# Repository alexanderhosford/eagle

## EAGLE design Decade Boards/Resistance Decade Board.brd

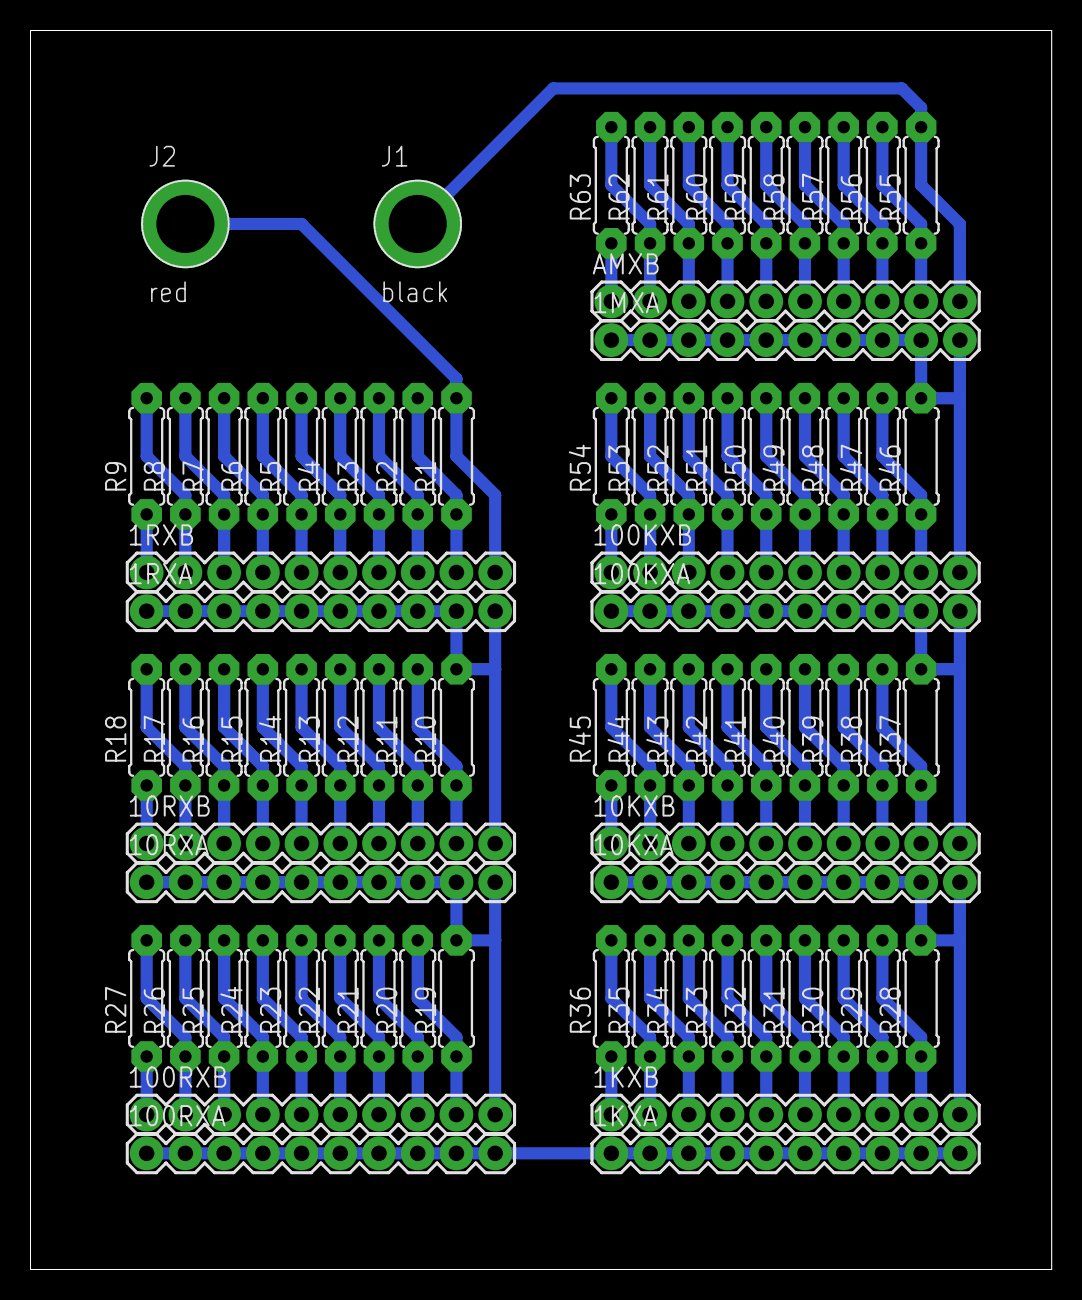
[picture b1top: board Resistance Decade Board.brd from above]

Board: 2 copper layers, 67.0 x 81.3 mm, 79 parts (0 on the bottom side), 71 nets.

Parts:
1KXA, 1KXB, 1MXA, 1RXA, 1RXB, 10KXA, 10KXB, 10RXA, 10RXB, 100KXA, 100KXB, 100RXA, 100RXB: M10"; 1X10
AMXB: M10"; 1X10
J1: black; BANANA_CONN
J2: red; BANANA_CONN
R1, R2, R3, R4, R5, R6, R7, R8, R9: 1R; 0207/7
R10, R11, R12, R13, R14, R15, R16, R17, R18: 10R; 0207/7
R19, R20, R21, R22, R23, R24, R25, R26, R27: 100R; 0207/7
R28, R29, R30, R31, R32, R33, R34, R35, R36: 1k; 0207/7
R37, R38, R39, R40, R41, R42, R43, R44, R45: 10k; 0207/7
R46, R47, R48, R49, R50, R51, R52, R53, R54: 100k; 0207/7
R55, R56, R57, R58, R59, R60, R61, R62, R63: 1M; 0207/7

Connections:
100KX: 100KXB.8, R47.1, R48.2
unnamed: 1RXB.2, R8.1, R9.2
unnamed: 1RXB.3, R7.1, R8.2
unnamed: 1RXB.4, R6.1, R7.2
unnamed: 1RXB.5, R5.1, R6.2
unnamed: 1RXB.6, R4.1, R5.2
unnamed: 1RXB.7, R3.1, R4.2
unnamed: 1RXB.8, R2.1, R3.2
unnamed: 1RXB.9, R1.1, R2.2
unnamed: 1RXB.10, J2.P$1, R1.2
unnamed: 1RXA.1, 1RXA.2, 1RXA.3, 1RXA.4, 1RXA.5, 1RXA.6, 1RXA.7, 1RXA.8, 1RXA.9, 1RXA.10, 10RXB.10, R10.2
unnamed: 10RXA.1, 10RXA.2, 10RXA.3, 10RXA.4, 10RXA.5, 10RXA.6, 10RXA.7, 10RXA.8, 10RXA.9, 10RXA.10, 100RXB.10, R19.2
unnamed: 1KXB.10, 10KXA.1, 10KXA.2, 10KXA.3, 10KXA.4, 10KXA.5, 10KXA.6, 10KXA.7, 10KXA.8, 10KXA.9, 10KXA.10, R28.2
unnamed: 10KXB.10, 100KXA.1, 100KXA.2, 100KXA.3, 100KXA.4, 100KXA.5, 100KXA.6, 100KXA.7, 100KXA.8, 100KXA.9, 100KXA.10, R37.2
unnamed: AMXB.10, J1.P$1, R55.2
unnamed: 1RXB.1, R9.1
unnamed: 10RXB.2, R17.1, R18.2
unnamed: 10RXB.3, R16.1, R17.2
unnamed: 10RXB.4, R15.1, R16.2
unnamed: 10RXB.5, R14.1, R15.2
unnamed: 10RXB.6, R13.1, R14.2
unnamed: 10RXB.7, R12.1, R13.2
unnamed: 10RXB.8, R11.1, R12.2
unnamed: 10RXB.9, R10.1, R11.2
unnamed: 10RXB.1, R18.1
unnamed: 100RXB.2, R26.1, R27.2
unnamed: 100RXB.3, R25.1, R26.2
unnamed: 100RXB.4, R24.1, R25.2
unnamed: 100RXB.5, R23.1, R24.2
unnamed: 100RXB.6, R22.1, R23.2
unnamed: 100RXB.7, R21.1, R22.2
unnamed: 100RXB.8, R20.1, R21.2
unnamed: 100RXB.9, R19.1, R20.2
unnamed: 100RXB.1, R27.1
unnamed: 1KXB.2, R35.1, R36.2
unnamed: 1KXB.3, R34.1, R35.2
unnamed: 1KXB.4, R33.1, R34.2
unnamed: 1KXB.5, R32.1, R33.2
unnamed: 1KXB.6, R31.1, R32.2
unnamed: 1KXB.7, R30.1, R31.2
unnamed: 1KXB.8, R29.1, R30.2
unnamed: 1KXB.9, R28.1, R29.2
unnamed: 1KXB.1, R36.1
unnamed: 10KXB.2, R44.1, R45.2
unnamed: 10KXB.3, R43.1, R44.2
unnamed: 10KXB.4, R42.1, R43.2
unnamed: 10KXB.5, R41.1, R42.2
unnamed: 10KXB.6, R40.1, R41.2
unnamed: 10KXB.7, R39.1, R40.2
unnamed: 10KXB.8, R38.1, R39.2
unnamed: 10KXB.9, R37.1, R38.2
unnamed: 10KXB.1, R45.1
unnamed: 100KXB.2, R53.1, R54.2
unnamed: 100KXB.3, R52.1, R53.2
unnamed: 100KXB.4, R51.1, R52.2
unnamed: 100KXB.5, R50.1, R51.2
unnamed: 100KXB.6, R49.1, R50.2
unnamed: 100KXB.7, R48.1, R49.2
unnamed: 100KXB.9, R46.1, R47.2
unnamed: 100KXB.1, R54.1
unnamed: AMXB.2, R62.1, R63.2
unnamed: AMXB.3, R61.1, R62.2
unnamed: AMXB.4, R60.1, R61.2
unnamed: AMXB.5, R59.1, R60.2
unnamed: AMXB.6, R58.1, R59.2
unnamed: AMXB.7, R57.1, R58.2
unnamed: AMXB.8, R56.1, R57.2
unnamed: AMXB.9, R55.1, R56.2
unnamed: AMXB.1, R63.1
unnamed: 1MXA.1, 1MXA.2, 1MXA.3, 1MXA.4, 1MXA.5, 1MXA.6, 1MXA.7, 1MXA.8, 1MXA.9, 1MXA.10, 100KXB.10, R46.2
unnamed: 1KXA.1, 1KXA.2, 1KXA.3, 1KXA.4, 1KXA.5, 1KXA.6, 1KXA.7, 1KXA.8, 1KXA.9, 1KXA.10, 100RXA.1, 100RXA.2, 100RXA.3, 100RXA.4, 100RXA.5, 100RXA.6, 100RXA.7, 100RXA.8, 100RXA.9, 100RXA.10

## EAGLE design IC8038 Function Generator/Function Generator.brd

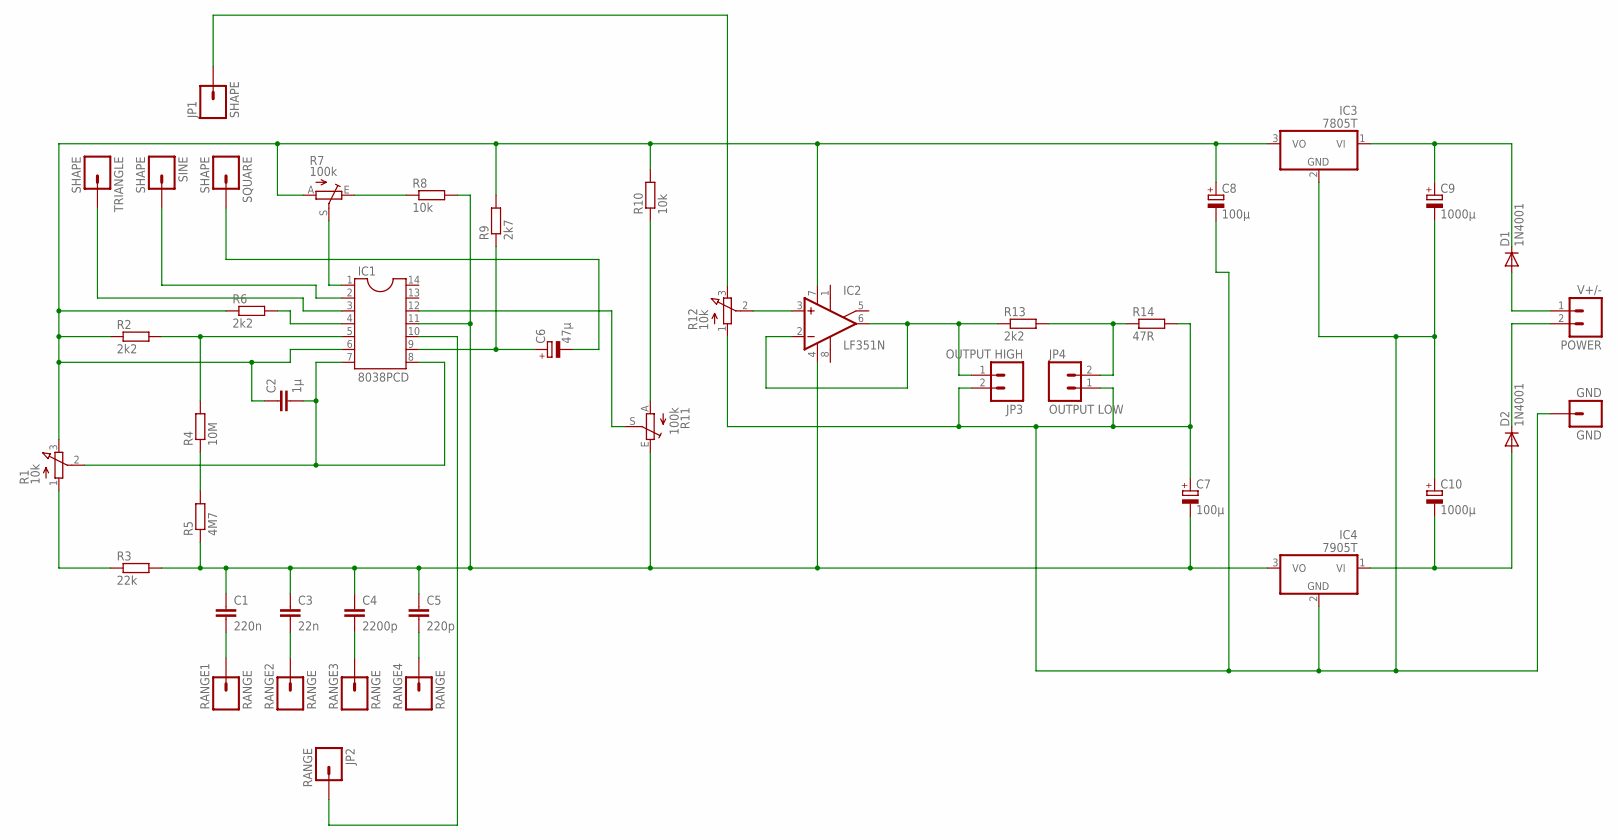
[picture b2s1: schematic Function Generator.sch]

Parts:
C1: 220n; C050-035X075
C2: 1µ; C050-035X075
C3: 22n; C050-035X075
C4: 2200p; C050-035X075
C5: 220p; C050-035X075
C6: 47µ; E5-10,5
C7, C8: 100µ; E3,5-8
C9, C10: 1000µ; E5-10,5
D1, D2: 1N4001; DO41-10
GND: GND; 1X01_LONGPAD
IC1: 8038PCD; DIL14
IC2: LF351N; DIL08
IC3: 7805T; TO220H
IC4: 7905T; TO220H
JP1: SHAPE; 1X01_LONGPAD
JP2: RANGE; 1X01_LONGPAD
JP3: OUTPUT HIGH; SCREWTERMINAL-3.5MM-2
JP4: OUTPUT LOW; SCREWTERMINAL-3.5MM-2
POWER: V+/-; SCREWTERMINAL-3.5MM-2
R1, R12: 10k; 3RP/1610N
R2, R6, R13: 2k2; 0207/10
R3: 22k; 0207/10
R4: 10M; 0207/10
R5: 4M7; 0207/10
R7, R11: 100k; S64Y
R8, R10: 10k; 0207/10
R9: 2k7; 0207/10
R14: 47R; 0207/10
RANGE1, RANGE2, RANGE3, RANGE4: RANGE; 1X01_LONGPAD
SINE: SHAPE; 1X01_LONGPAD
SQUARE: SHAPE; 1X01_LONGPAD
TRIANGLE: SHAPE; 1X01_LONGPAD

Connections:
GND: C7.+, C8.-, C9.-, C10.+, GND.1, IC3.2 (GND), IC4.2 (GND), JP3.2, JP4.1, R12.1 (A), R14.2
unnamed: IC1.4 (DUTYCYCLE), R6.2
unnamed: IC1.5 (FREQUENCYADJUST), R2.2, R4.2
unnamed: C2.1, C8.+, IC1.6 (V+), IC2.7 (V+), IC3.3 (VO), R1.3 (E), R2.1, R6.1, R7.A, R9.2, R10.2
unnamed: C2.2, IC1.7 (FMBIAS), IC1.8 (FMSWEEPINPUT), R1.2 (S)
unnamed: R4.1, R5.2
unnamed: C1.1, C3.1, C4.1, C5.1, C7.-, IC1.11 (V-ORGROUND), IC2.4 (V-), IC4.3 (VO), R3.2, R5.1, R8.2, R11.E
unnamed: R1.1 (A), R3.1
unnamed: C3.2, RANGE2.1
unnamed: C4.2, RANGE3.1
unnamed: C1.2, RANGE1.1
unnamed: C5.2, RANGE4.1
unnamed: IC1.10 (TIMINGCAPACITOR), JP2.1
unnamed: C6.+, IC1.9 (SQUAREWAVEOUT), R9.1
unnamed: R7.E, R8.1
unnamed: IC2.2 (-IN), IC2.6 (OUT), JP3.1, R13.1
unnamed: IC1.3 (TRIANGLEOUT), TRIANGLE.1
unnamed: IC1.2 (SINEWAVEOUT), SINE.1
unnamed: IC1.1 (SINEWAVEADJUST), R7.S
unnamed: C6.-, SQUARE.1
unnamed: R10.1, R11.A
unnamed: IC1.12 (SINEWAVEADJUST2), R11.S
unnamed: IC2.3 (+IN), R12.2 (S)
unnamed: JP1.1, R12.3 (E)
unnamed: JP4.2, R13.2, R14.1
unnamed: C10.-, D2.A, IC4.1 (VI)
unnamed: C9.+, D1.C, IC3.1 (VI)
unnamed: D1.A, POWER.1
unnamed: D2.C, POWER.2

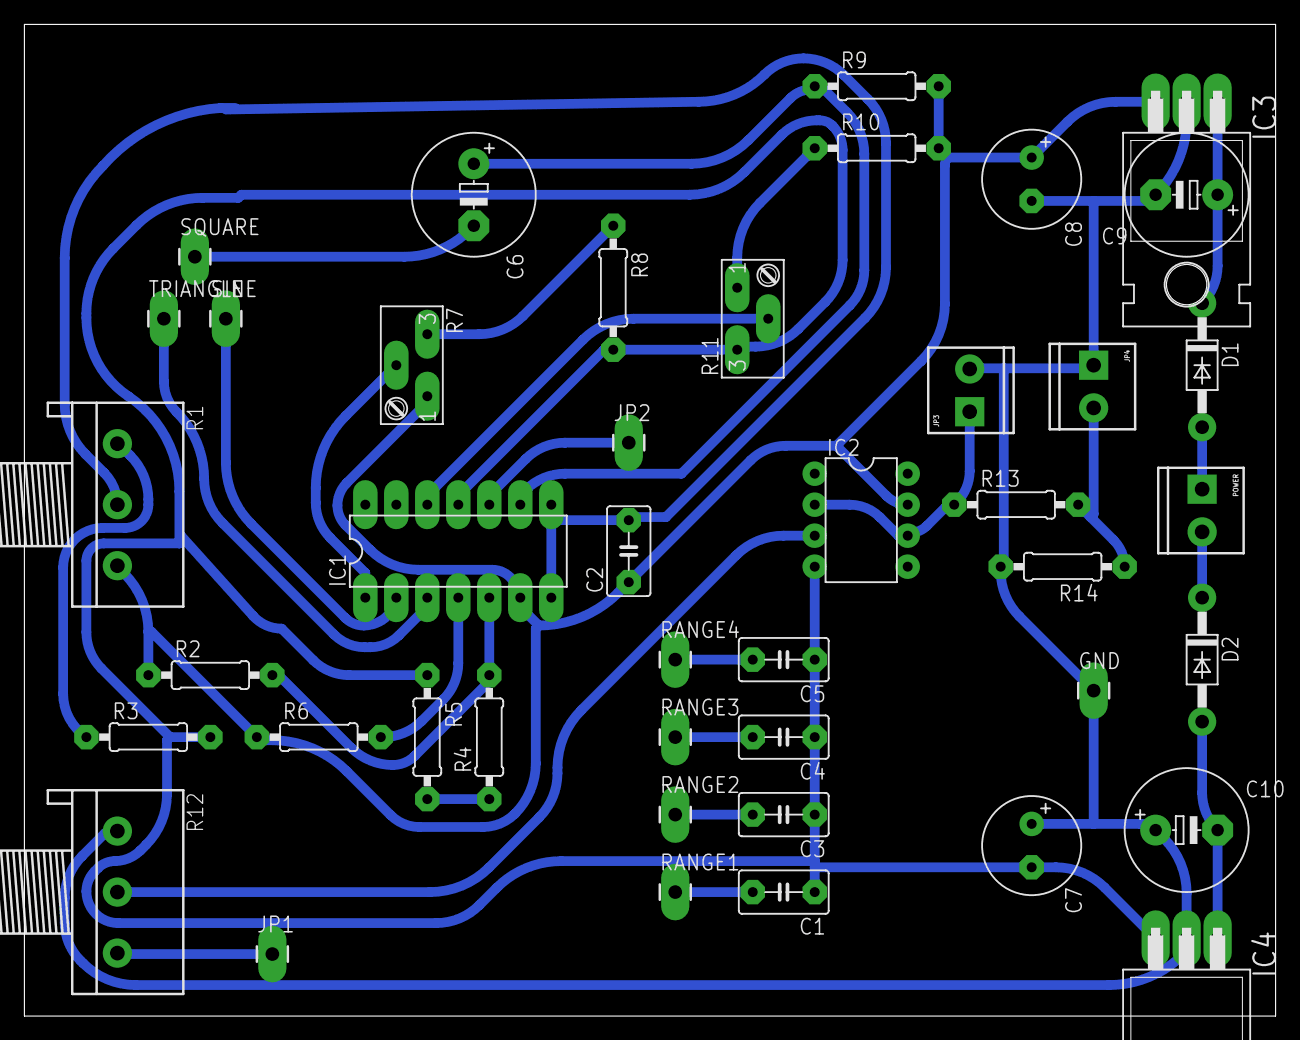
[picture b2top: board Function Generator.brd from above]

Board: 2 copper layers, 102.5 x 81.3 mm, 43 parts (0 on the bottom side), 29 nets.

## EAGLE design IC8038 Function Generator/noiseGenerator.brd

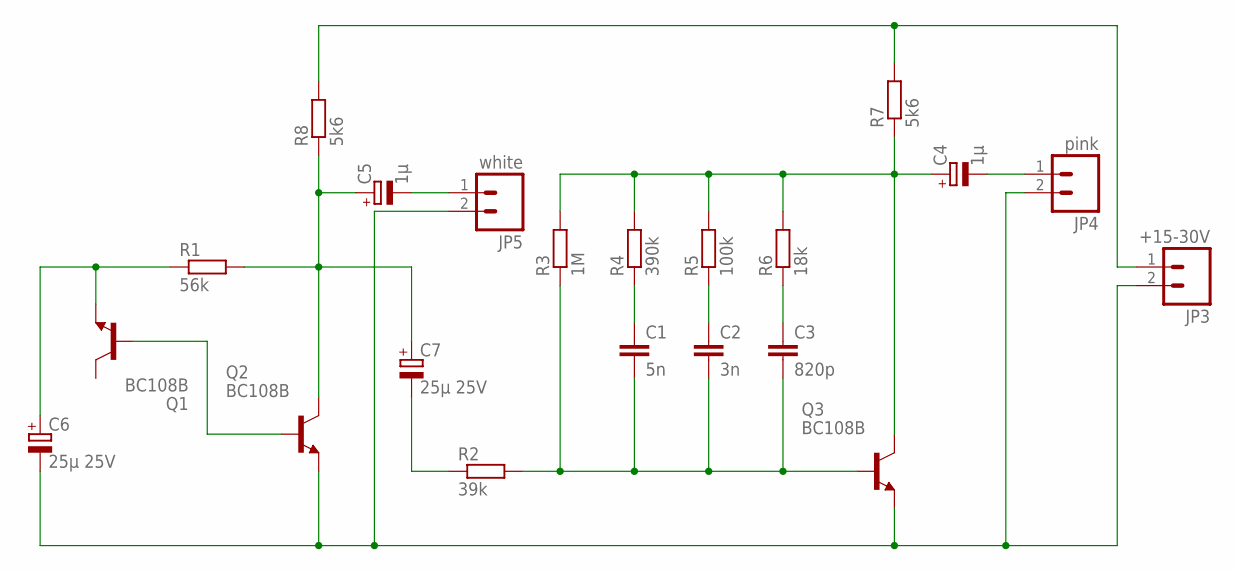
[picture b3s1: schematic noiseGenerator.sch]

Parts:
C1: 5n; C050-035X075
C2: 3n; C050-035X075
C3: 820p; C050-035X075
C4, C5: 1µ; E5-8,5
C6, C7: 25µ 25V; E5-8,5
JP3: +15-30V; SCREWTERMINAL-3.5MM-2
JP4: pink; SCREWTERMINAL-3.5MM-2
JP5: white; SCREWTERMINAL-3.5MM-2
Q1, Q2, Q3: BC108B; TO18
R1: 56k; 0207/10
R2: 39k; 0207/10
R3: 1M; 0207/10
R4: 390k; 0207/10
R5: 100k; 0207/10
R6: 18k; 0207/10
R7, R8: 5k6; 0207/10

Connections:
GND: C6.-, JP3.2, JP4.2, JP5.2, Q2.1 (E), Q3.1 (E)
unnamed: C4.-, JP4.1
unnamed: C4.+, Q3.3 (C), R3.2, R4.2, R5.2, R6.2, R7.1
unnamed: C1.1, R4.1
unnamed: C2.1, R5.1
unnamed: C3.1, R6.1
unnamed: C1.2, C2.2, C3.2, Q3.2 (B), R2.2, R3.1
unnamed: JP3.1, R7.2, R8.2
unnamed: C5.+, C7.+, Q2.3 (C), R1.2, R8.1
unnamed: C5.-, JP5.1
unnamed: C7.-, R2.1
unnamed: C6.+, Q1.1 (E), R1.1
unnamed: Q1.2 (B), Q2.2 (B)

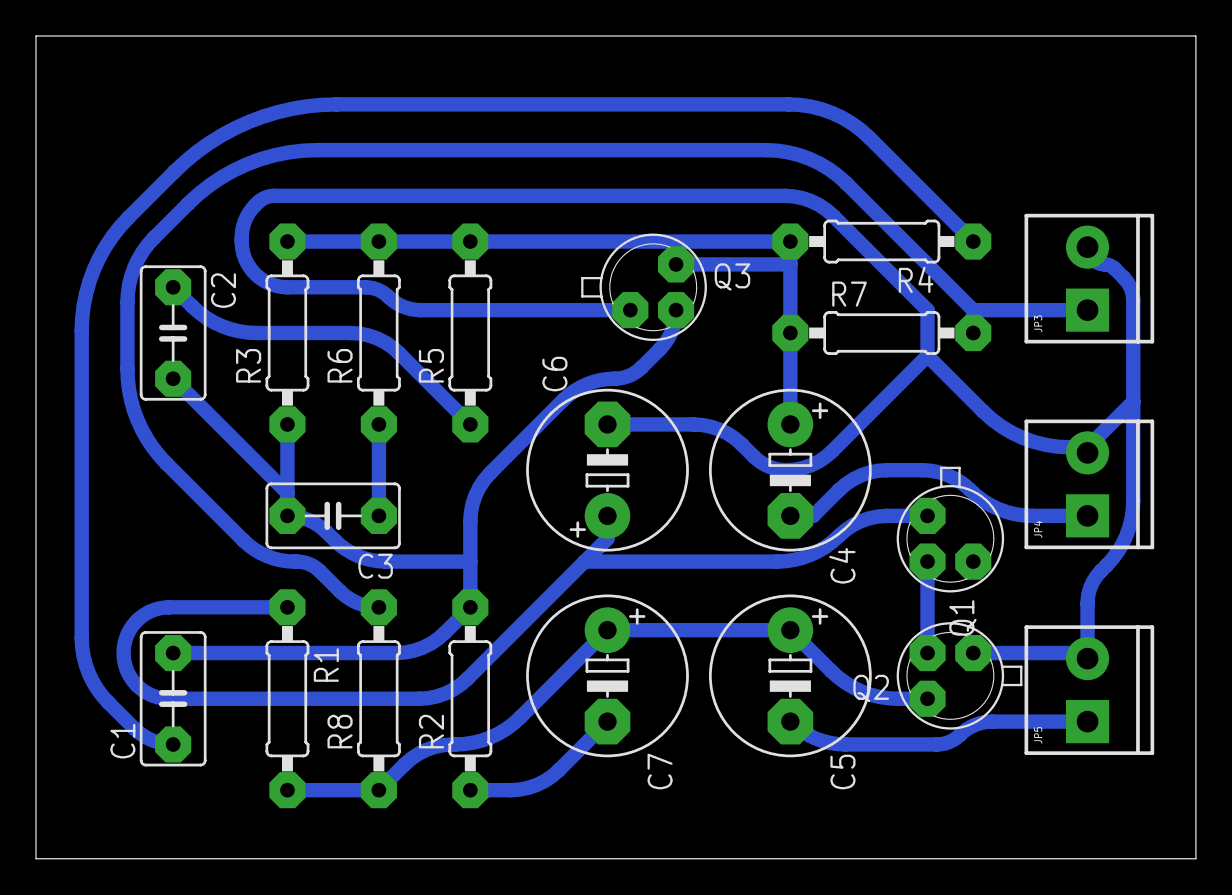
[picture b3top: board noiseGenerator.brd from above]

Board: 2 copper layers, 64.4 x 45.7 mm, 21 parts (0 on the bottom side), 13 nets.

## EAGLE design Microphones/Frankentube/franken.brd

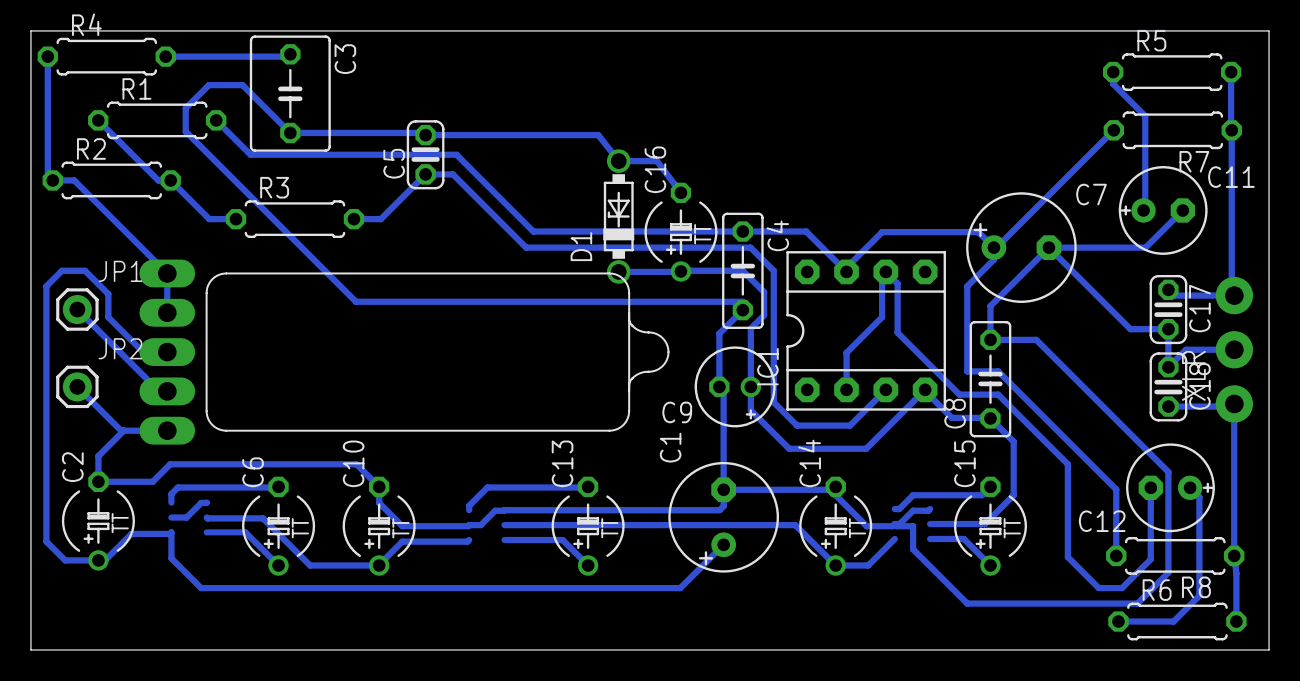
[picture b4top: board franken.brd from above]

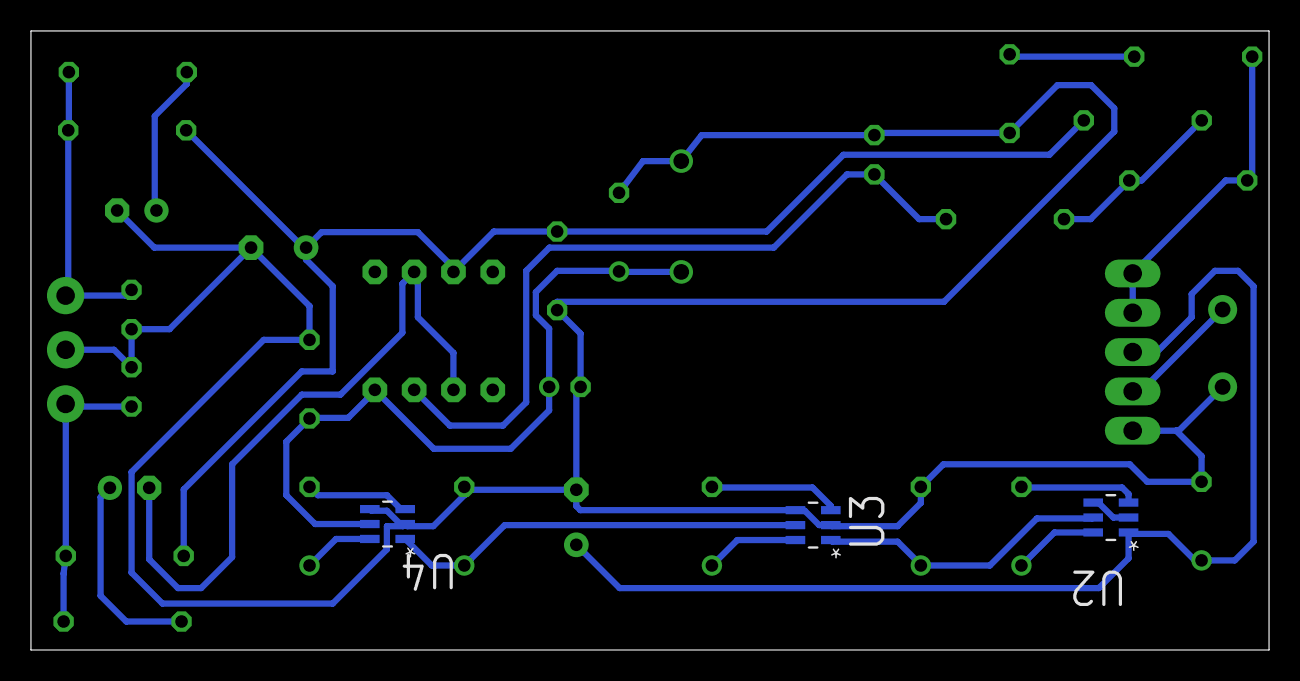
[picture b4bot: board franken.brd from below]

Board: 2 copper layers, 80.0 x 40.0 mm, 35 parts (3 on the bottom side), 23 nets.

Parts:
C1: 470µ 16V; E3,5-8
C2, C6, C10, C13, C14, C15, C16: 4µ7 10V; TAP5-45
C3: 1µ 50V; C050-050X075
C4, C8: 100n 50V; C050-025X075
C5: 22p 50V; C025-024X044
C7: 100µ 50V; E3,5-8
C9: 100µ 16V; E2-5
C11, C12: 47µ 50V; E2,5-6E
C17, C18: 22n; C025-024X044
D1: 10V; 7MMGRIDZENER
IC1: OPA134P; DIL08
JP1: 1G; 1X01
JP2: GND_RETURN; 1X01
R1: 82k; 0207/7
R2: 33k; 0207/7
R3: 4k7; 0207/7
R4: 330k; 0207/7
R5, R6: 150R; 0207/7
R7, R8: 2k2; 0207/7
U1: JAN-6418; SUBMINIATURE_PENTODE
U2, U3, U4: LM2665M6; SOT95P285X120-6N
XLR: INPUT; 3.5MM_PADS

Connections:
GND: U2.2, U2.4
unnamed: C4.1, C7.+, IC1.7, R1.2, R7.2, R8.2
unnamed: R2.1, R4.1, U1.1, U1.2
unnamed: C3.1, R4.2
unnamed: R1.1, R2.2, R3.1
unnamed: C5.1, IC1.3, R3.2
unnamed: C6.+, U2.6
unnamed: C8.1, C9.+, C16.+, D1.C, IC1.4, U4.5
unnamed: C6.-, U2.3
unnamed: C12.-, IC1.2, IC1.6
unnamed: C12.+, R6.1
unnamed: C11.+, R5.1
unnamed: C18.2, R6.2, R8.1, XLR.1
unnamed: C17.1, R5.2, R7.1, XLR.3
unnamed: JP1.1, U1.4
unnamed: C1.+, C2.+, U1.3, U2.1
unnamed: C13.+, U3.6
unnamed: C13.-, U3.3
unnamed: C15.+, U4.6
unnamed: C15.-, U4.3
unnamed: C10.+, U2.5, U3.1
unnamed: C14.+, U3.5, U4.1
PE: C1.-, C2.-, C3.2, C4.2, C5.2, C7.-, C8.2, C9.-, C10.-, C11.-, C14.-, C16.-, C17.2, C18.1, D1.A, JP2.1, U1.5, U3.2, U3.4, U4.2, U4.4, XLR.2

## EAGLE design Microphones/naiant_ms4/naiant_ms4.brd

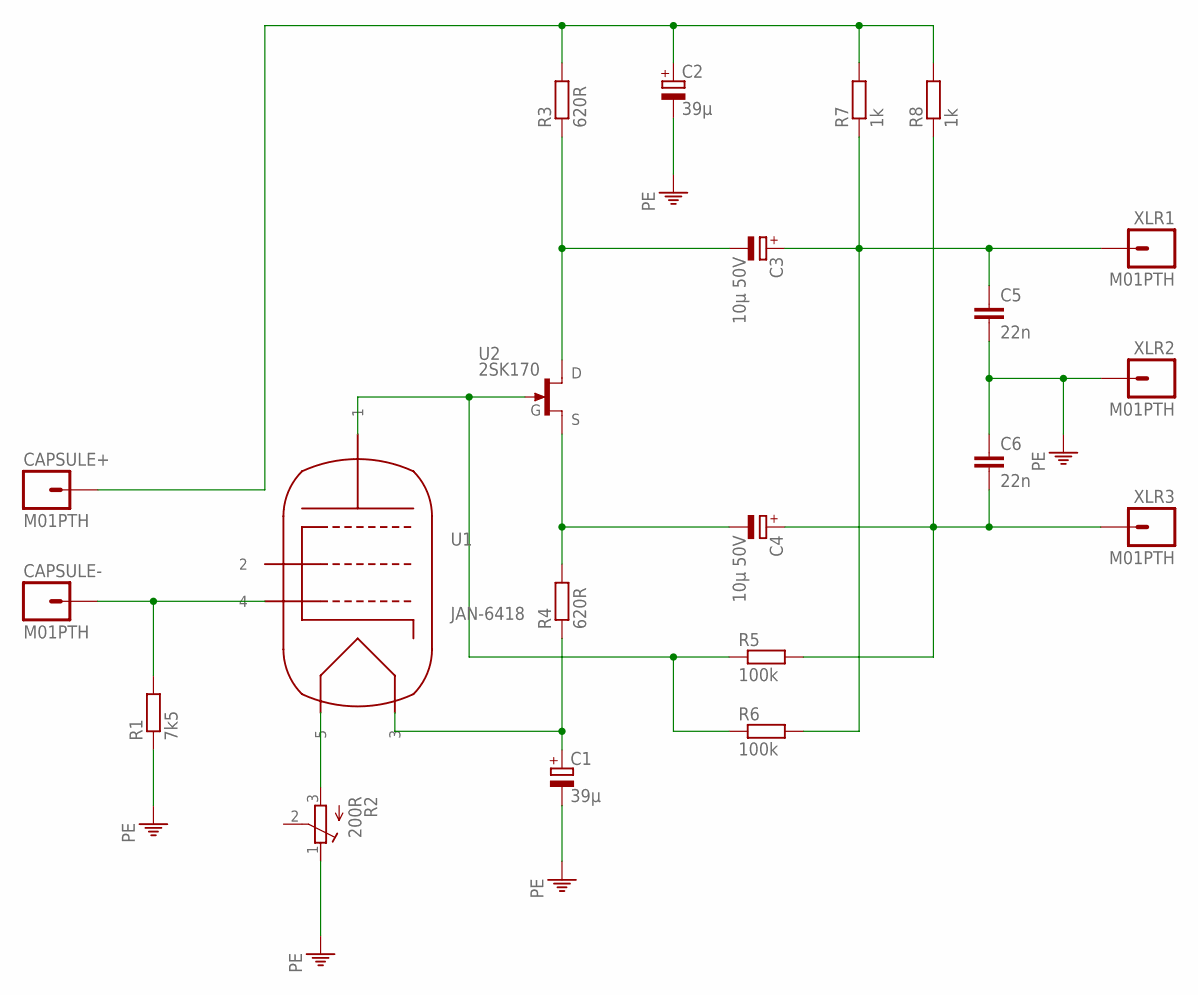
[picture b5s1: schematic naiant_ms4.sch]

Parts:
C1, C2: 39µ; E2,5-6E
C3, C4: 10µ 50V; E2-5
C5, C6: 22n; C050-024X044
CAPSULE+: M01PTH; 1X01
CAPSULE-: M01PTH; 1X01
R1: 7k5; 0207/7
R2: 200R; RTRIM3006P
R3, R4: 620R; 0207/7
R5, R6: 100k; 0207/7
R7, R8: 1k; 0207/7
U1: JAN-6418; SUBMINIATURE_PENTODE
U2: 2SK170; TO92-
XLR1, XLR2, XLR3: M01PTH; 1X01

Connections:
unnamed: C3.+, C5.1, R6.2, R7.1, XLR1.1
unnamed: C4.+, C6.2, R5.2, R8.1, XLR3.1
unnamed: C3.-, R3.1, U2.1 (D)
unnamed: C4.-, R4.2, U2.3 (S)
unnamed: C1.+, R4.1, U1.3
unnamed: C2.+, CAPSULE+.1, R3.2, R7.2, R8.2
unnamed: R2.3 (E), U1.5
unnamed: CAPSULE-.1, R1.2, U1.4
unnamed: R5.1, R6.1, U1.1, U2.2 (G)
PE: C1.-, C2.-, C5.2, C6.1, R1.1, R2.1 (A), XLR2.1

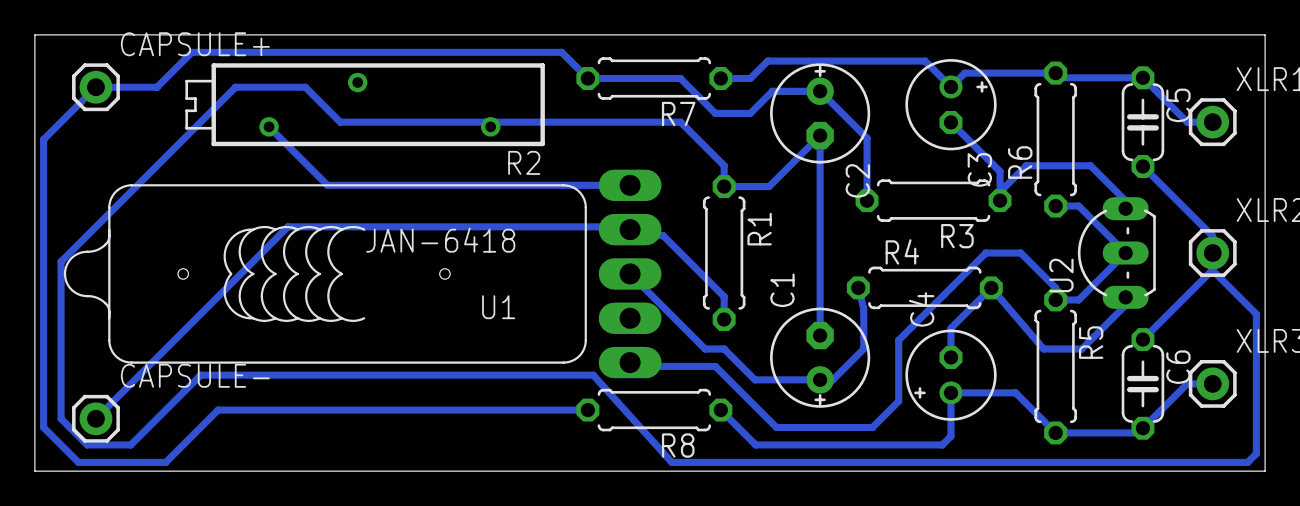
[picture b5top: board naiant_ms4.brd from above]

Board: 2 copper layers, 70.5 x 25.0 mm, 21 parts (0 on the bottom side), 10 nets.

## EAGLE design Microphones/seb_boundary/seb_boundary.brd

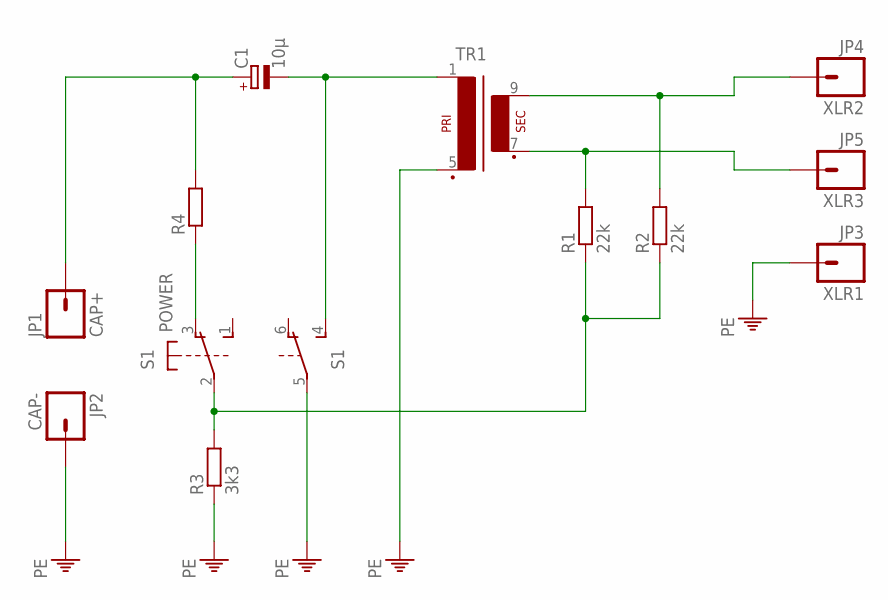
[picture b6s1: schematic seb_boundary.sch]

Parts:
C1: 10µ; E2,5-6
JP1: CAP+; 1X01
JP2: CAP-; 1X01
JP3: XLR1; 1X01
JP4: XLR2; 1X01
JP5: XLR3; 1X01
R1, R2: 22k; 0207/10
R3: 3k3; 0207/10
R4: R-EU_0207/10; 0207/10
S1: POWER; 9450-2
TR1: VV11

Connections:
unnamed: C1.+, JP1.1, R4.2
unnamed: R4.1, S1.3 (O)
unnamed: R1.1, R2.1, R3.2, S1.2
unnamed: C1.-, S1.4 (S), TR1.1
unnamed: JP5.1, R1.2, TR1.7 (S3)
unnamed: JP4.1, R2.2, TR1.9 (S4)
PE: JP2.1, JP3.1, R3.1, S1.5, TR1.5 (P2)

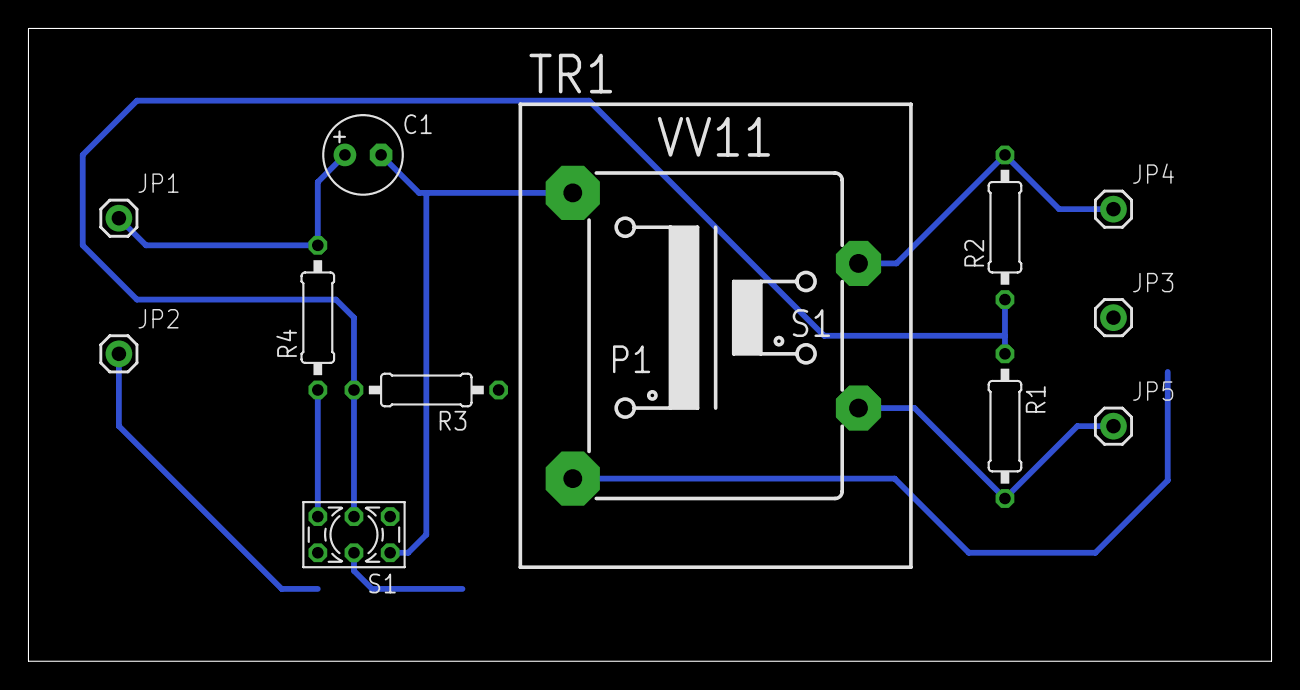
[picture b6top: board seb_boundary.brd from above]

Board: 2 copper layers, 87.3 x 44.4 mm, 12 parts (0 on the bottom side), 7 nets.

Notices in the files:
parts and their libraries:
SparkFun: Licensing: CC v3.0 Share-Alike You are welcome to use this library for commercial purposes.
